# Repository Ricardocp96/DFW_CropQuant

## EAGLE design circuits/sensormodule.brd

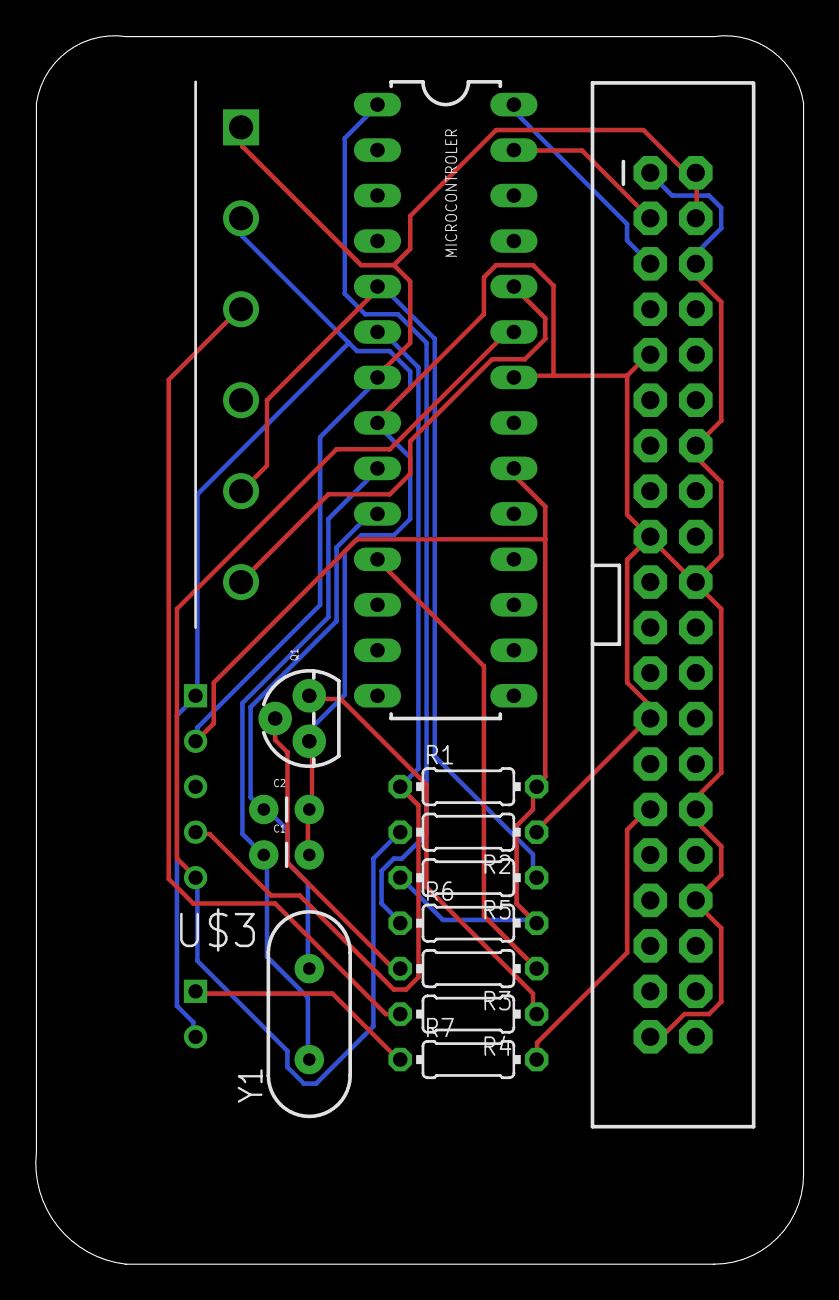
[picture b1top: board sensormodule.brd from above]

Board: 2 copper layers, 42.9 x 68.6 mm, 16 parts (0 on the bottom side), 17 nets.

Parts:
C1, C2: 22pF; CAP-PTH-SMALL
ENVIRONMENTAL_SENSOR: ENV_OUT
MICROCONTROLER: ATMEGA328P_PDIP; DIL28-3
Q1: TO-92
R1, R2: 10K; 0204/7
R3: 1K; 0204/7
R4: 100; 0204/7
R5, R6: 4.7K; 0204/7
R7: 68; 0204/7
SINGLE_BOARD_COMPUTER: RASPBERRYPI-40-PIN-GPIO; 2X20-SHROUDED
SOIL_SENSOR: SOIL_OUT
U$3: LED
Y1: 16MHz; HC49US

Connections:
3.3V: C1.2, C2.2, ENVIRONMENTAL_SENSOR.1, MICROCONTROLER.8, MICROCONTROLER.22, Q1.1, R2.1, SINGLE_BOARD_COMPUTER.1, SINGLE_BOARD_COMPUTER.6, SINGLE_BOARD_COMPUTER.9, SINGLE_BOARD_COMPUTER.14, SINGLE_BOARD_COMPUTER.17, SINGLE_BOARD_COMPUTER.20, SINGLE_BOARD_COMPUTER.25, SINGLE_BOARD_COMPUTER.30, SINGLE_BOARD_COMPUTER.34, SINGLE_BOARD_COMPUTER.39, SOIL_SENSOR.2, U$3.2
5V: ENVIRONMENTAL_SENSOR.2, MICROCONTROLER.7, MICROCONTROLER.20, R1.2, R5.2, R6.2, SINGLE_BOARD_COMPUTER.2, SINGLE_BOARD_COMPUTER.4, SOIL_SENSOR.1
unnamed: C1.1, MICROCONTROLER.9, Y1.1
unnamed: C2.1, MICROCONTROLER.10, Y1.2
unnamed: Q1.3, R4.1
unnamed: ENVIRONMENTAL_SENSOR.5, MICROCONTROLER.23, R2.2
unnamed: MICROCONTROLER.27, SINGLE_BOARD_COMPUTER.3
unnamed: MICROCONTROLER.5, R5.1, SOIL_SENSOR.5
unnamed: ENVIRONMENTAL_SENSOR.4, MICROCONTROLER.6, R1.1
unnamed: MICROCONTROLER.11, R3.1
unnamed: Q1.2, R3.2
unnamed: R4.2, SOIL_SENSOR.3
unnamed: MICROCONTROLER.24, SOIL_SENSOR.6
unnamed: MICROCONTROLER.28, SINGLE_BOARD_COMPUTER.5
unnamed: MICROCONTROLER.1, R6.1
unnamed: R7.1, U$3.1
unnamed: R7.2, SINGLE_BOARD_COMPUTER.29

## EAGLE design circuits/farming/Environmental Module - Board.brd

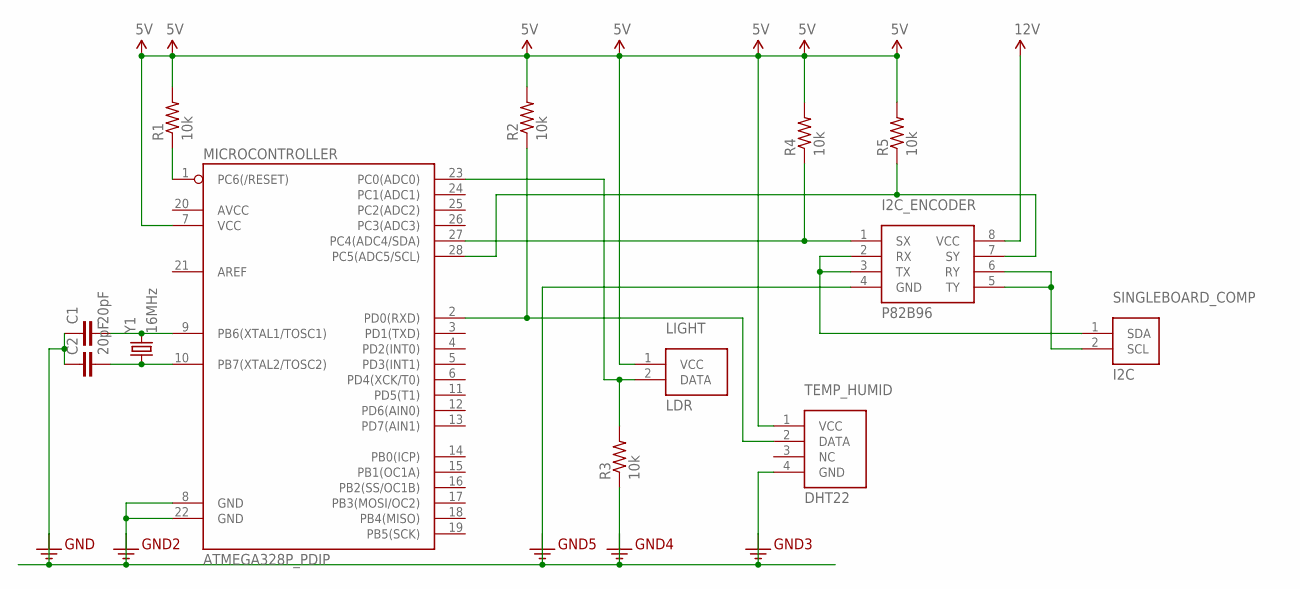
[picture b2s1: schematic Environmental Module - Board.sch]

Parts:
C1, C2: 20pF; CAP-PTH-SMALL
I2C_ENCODER: P82B96; SOIC8
LIGHT: LDR
MICROCONTROLLER: ATMEGA328P_PDIP; DIL28-3
R1, R2, R3, R4, R5: 10k; 0204/7
SINGLEBOARD_COMP: I2C; LDR
TEMP_HUMID: DHT22
Y1: 16MHz; HC49US

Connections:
3.3V: C1.1, C2.1, I2C_ENCODER.4 (GND), MICROCONTROLLER.8 (GND), MICROCONTROLLER.22 (GND), R3.1, TEMP_HUMID.4 (GND)
5V: LIGHT.1 (VCC), MICROCONTROLLER.7 (VCC), R1.2, R2.2, R4.2, R5.2, TEMP_HUMID.1 (VCC)
12V: I2C_ENCODER.8 (VCC)
unnamed: I2C_ENCODER.7 (SY), MICROCONTROLLER.28 (PC5(ADC5/SCL)), R5.1
unnamed: MICROCONTROLLER.1 (PC6(/RESET)), R1.1
unnamed: I2C_ENCODER.5 (TY), I2C_ENCODER.6 (RY), SINGLEBOARD_COMP.2 (SCL)
unnamed: I2C_ENCODER.1 (SX), MICROCONTROLLER.27 (PC4(ADC4/SDA)), R4.1
unnamed: MICROCONTROLLER.2 (PD0(RXD)), R2.1, TEMP_HUMID.2 (DATA)
unnamed: LIGHT.2 (DATA), MICROCONTROLLER.23 (PC0(ADC0)), R3.2
unnamed: I2C_ENCODER.2 (RX), I2C_ENCODER.3 (TX), SINGLEBOARD_COMP.1 (SDA)
unnamed: C2.2, MICROCONTROLLER.10 (PB7(XTAL2/TOSC2)), Y1.1
unnamed: C1.2, MICROCONTROLLER.9 (PB6(XTAL1/TOSC1)), Y1.2

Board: 2 copper layers, 13 parts (0 on the bottom side), 11 nets, no tracks yet.

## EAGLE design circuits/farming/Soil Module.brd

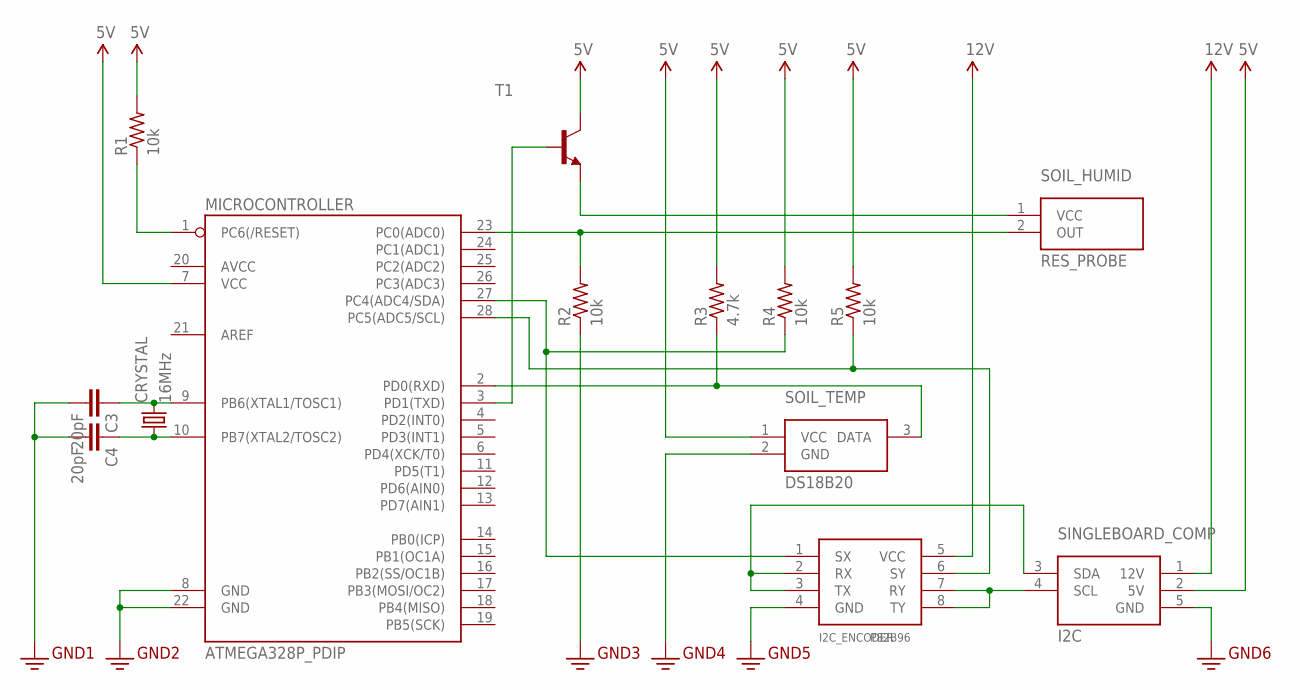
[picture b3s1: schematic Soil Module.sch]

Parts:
C3, C4: 20pF; CAP-PTH-SMALL
CRYSTAL: 16MHz; HC49US
I2C_ENCODER: P82B96; DIP08
MICROCONTROLLER: ATMEGA328P_PDIP; DIL28-3
R1, R2, R4, R5: 10k; 0204/7
R3: 4.7k; 0204/7
SINGLEBOARD_COMP: I2C; I2C_TERM
SOIL_HUMID: RES_PROBE; SOIL_MOISTURE
SOIL_TEMP: DS18B20; SOIL_TEMP
T1: 2N2222A-NPN-TO18-EBC; TO18

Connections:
3.3V: C3.2, C4.2, I2C_ENCODER.4 (GND), MICROCONTROLLER.8 (GND), MICROCONTROLLER.22 (GND), R2.1, SINGLEBOARD_COMP.5 (GND), SOIL_TEMP.2 (GND)
5V: MICROCONTROLLER.7 (VCC), R1.2, R3.2, R4.2, R5.2, SINGLEBOARD_COMP.2 (5V), SOIL_TEMP.1 (VCC), T1.3 (C)
12V: I2C_ENCODER.5 (VCC), SINGLEBOARD_COMP.1 (12V)
unnamed: I2C_ENCODER.6 (SY), MICROCONTROLLER.28 (PC5(ADC5/SCL)), R5.1
unnamed: I2C_ENCODER.1 (SX), MICROCONTROLLER.27 (PC4(ADC4/SDA)), R4.1
unnamed: I2C_ENCODER.2 (RX), I2C_ENCODER.3 (TX), SINGLEBOARD_COMP.3 (SDA)
unnamed: SOIL_HUMID.1 (VCC), T1.1 (E)
unnamed: MICROCONTROLLER.3 (PD1(TXD)), T1.2 (B)
unnamed: MICROCONTROLLER.2 (PD0(RXD)), R3.1, SOIL_TEMP.3 (DATA)
unnamed: MICROCONTROLLER.23 (PC0(ADC0)), R2.2, SOIL_HUMID.2 (OUT)
unnamed: C4.1, CRYSTAL.1, MICROCONTROLLER.10 (PB7(XTAL2/TOSC2))
unnamed: C3.1, CRYSTAL.2, MICROCONTROLLER.9 (PB6(XTAL1/TOSC1))
unnamed: MICROCONTROLLER.1 (PC6(/RESET)), R1.1
unnamed: I2C_ENCODER.7 (RY), I2C_ENCODER.8 (TY), SINGLEBOARD_COMP.4 (SCL)

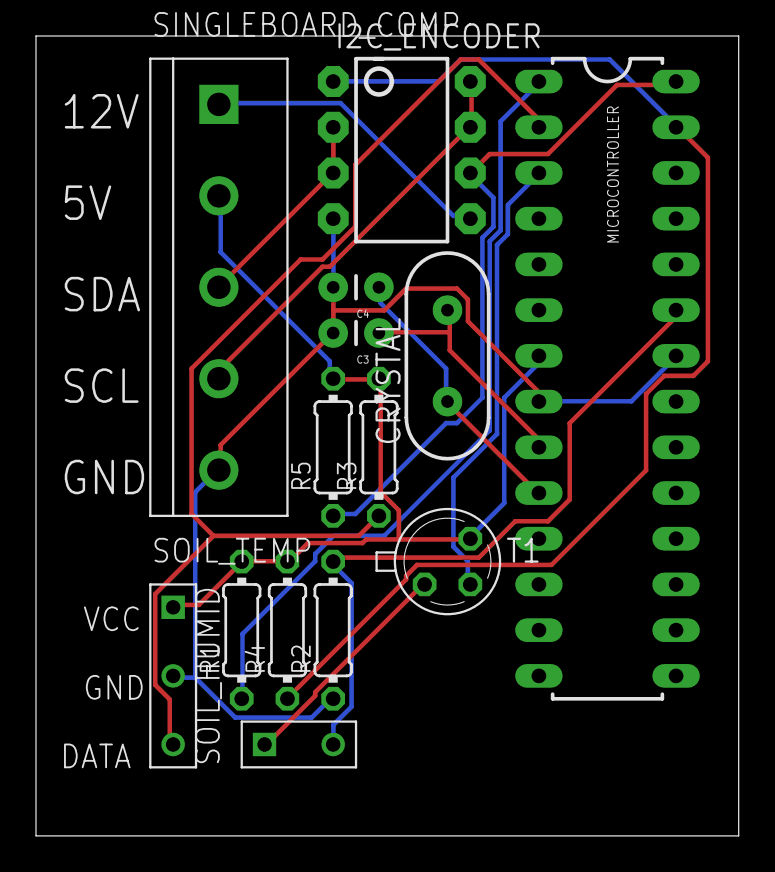
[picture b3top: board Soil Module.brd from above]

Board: 2 copper layers, 39.0 x 44.4 mm, 14 parts (0 on the bottom side), 14 nets.

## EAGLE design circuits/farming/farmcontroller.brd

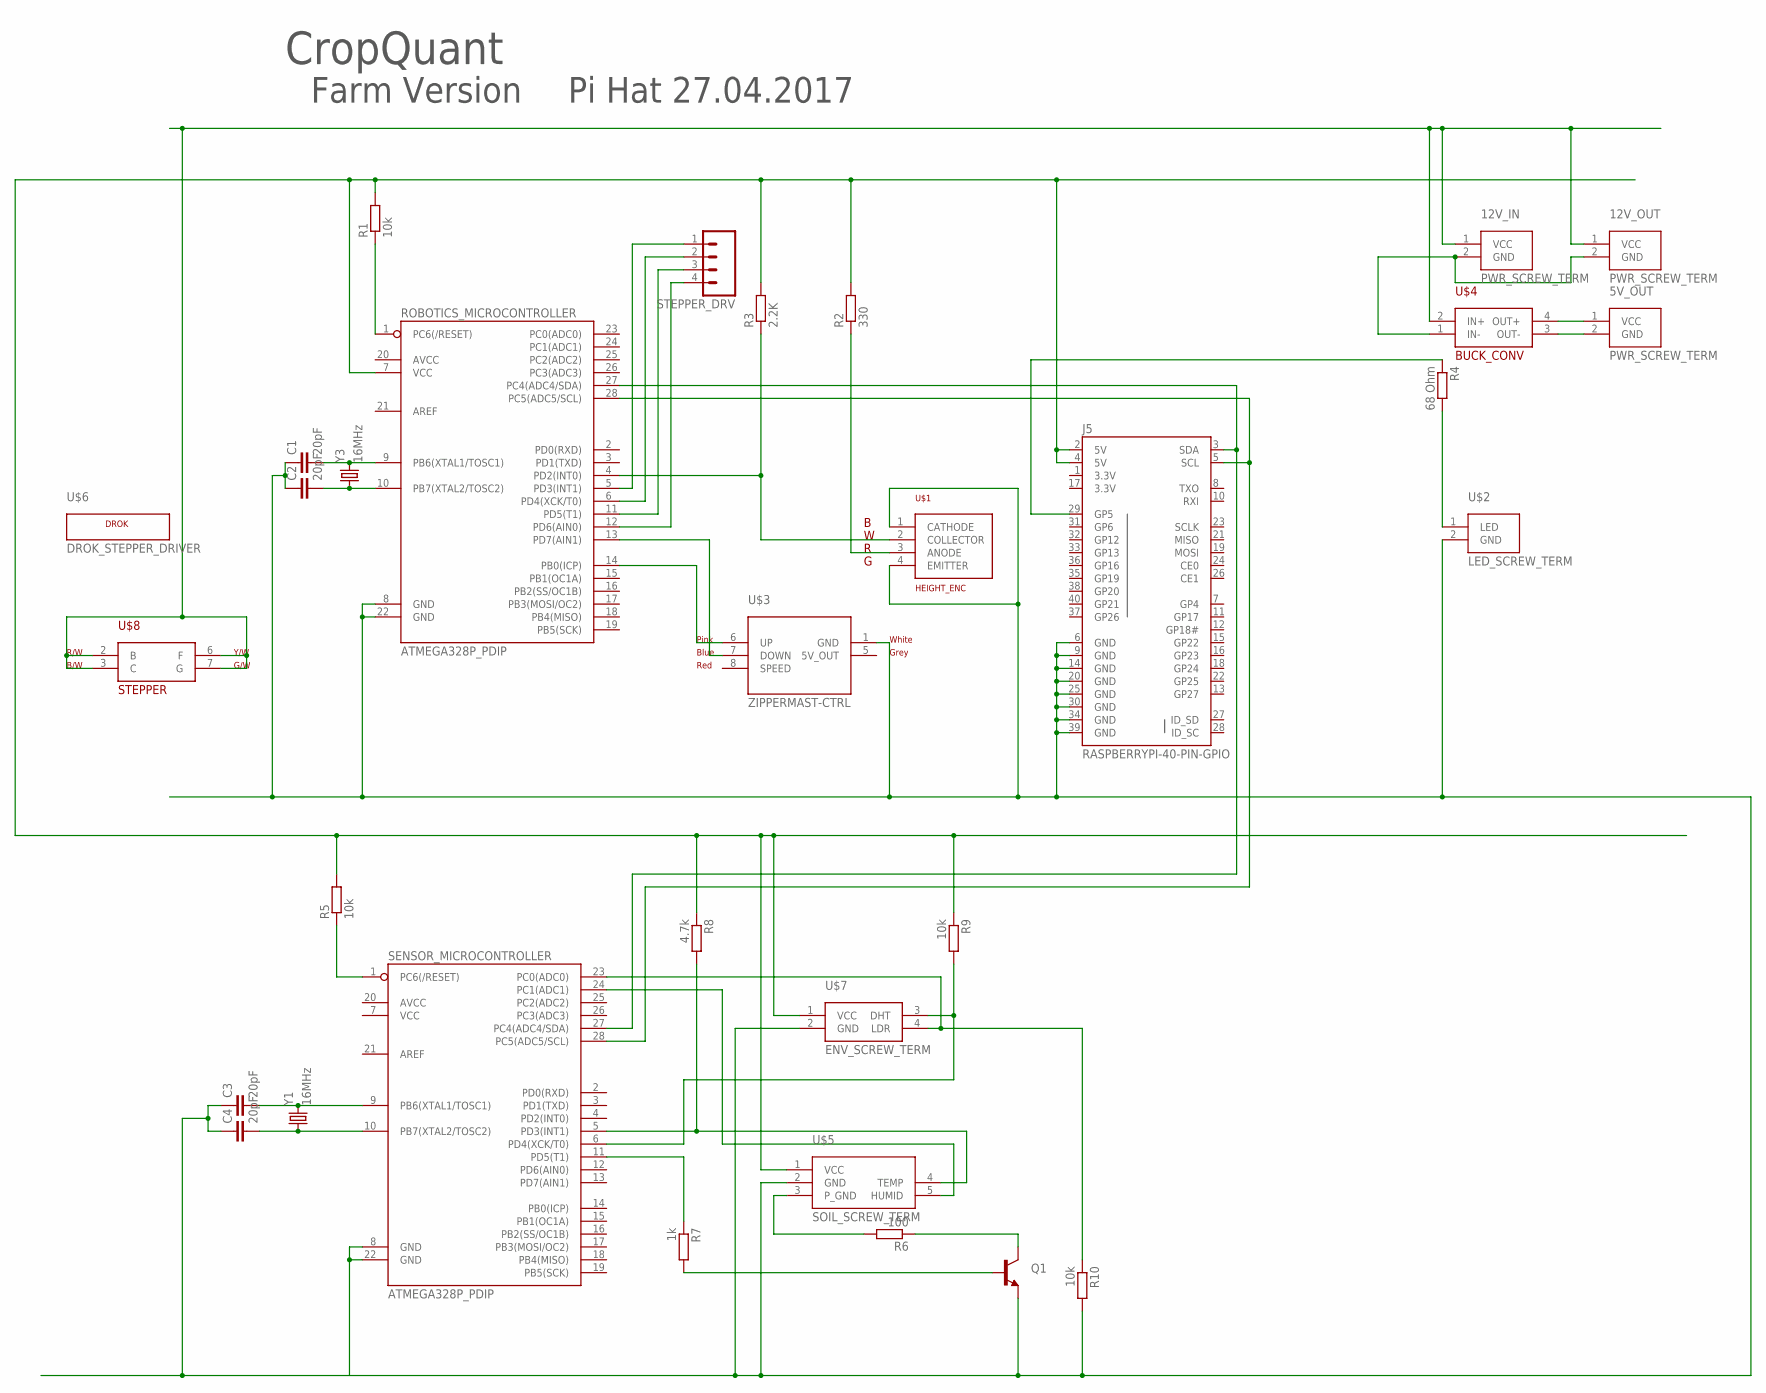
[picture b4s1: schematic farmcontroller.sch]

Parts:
5V_OUT, 12V_IN, 12V_OUT: PWR_SCREW_TERM
C1, C2, C3, C4: 20pF; CAP-PTH-SMALL
J5: RASPBERRYPI-40-PIN-GPIO; 2X20-SHROUDED
Q1: TRANSISTOR_NPNP2N2222A; TO-92
R1, R5, R9, R10: 10k; 0204/7
R2: 330; 0204/7
R3: 2.2K; 0204/7
R4: 68 Ohm; 0204/7
R6: 100; 0204/7
R7: 1k; 0204/7
R8: 4.7k; 0204/7
ROBOTICS_MICROCONTROLLER: ATMEGA328P_PDIP; DIL28-3
SENSOR_MICROCONTROLLER: ATMEGA328P_PDIP; DIL28-3
STEPPER_DRV: M04PTH; 1X04
U$1: HEIGHT_ENC
U$2: LED_SCREW_TERM
U$3: ZIPPERMAST-CTRL
U$4: BUCK_CONV
U$5: SOIL_SCREW_TERM
U$6: DROK_STEPPER_DRIVER
U$7: ENV_SCREW_TERM
U$8: STEPPER
Y1, Y3: 16MHz; HC49US

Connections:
3.3V: J5.1 (3.3V), J5.17 (3.3V)
unnamed: R6.2, U$5.3 (P_GND)
unnamed: J5.2 (5V), J5.4 (5V), R1.2, R2.2, R3.2, R5.2, R8.1, R9.1, ROBOTICS_MICROCONTROLLER.7 (VCC), U$5.1 (VCC), U$7.1 (VCC)
unnamed: R1.1, ROBOTICS_MICROCONTROLLER.1 (PC6(/RESET))
unnamed: J5.3 (SDA), ROBOTICS_MICROCONTROLLER.27 (PC4(ADC4/SDA)), SENSOR_MICROCONTROLLER.27 (PC4(ADC4/SDA))
unnamed: J5.5 (SCL), ROBOTICS_MICROCONTROLLER.28 (PC5(ADC5/SCL)), SENSOR_MICROCONTROLLER.28 (PC5(ADC5/SCL))
unnamed: ROBOTICS_MICROCONTROLLER.14 (PB0(ICP)), U$3.6 (UP)
unnamed: ROBOTICS_MICROCONTROLLER.13 (PD7(AIN1)), U$3.7 (DOWN)
unnamed: R5.1, SENSOR_MICROCONTROLLER.1 (PC6(/RESET))
unnamed: R2.1, U$1.3 (ANODE)
unnamed: R3.1, ROBOTICS_MICROCONTROLLER.4 (PD2(INT0)), U$1.2 (COLLECTOR)
unnamed: 12V_IN.1 (VCC), 12V_OUT.1 (VCC), U$4.2 (IN+), U$8.2 (B), U$8.3 (C), U$8.6 (F), U$8.7 (G)
unnamed: C2.2, ROBOTICS_MICROCONTROLLER.10 (PB7(XTAL2/TOSC2)), Y3.1
unnamed: C3.2, SENSOR_MICROCONTROLLER.9 (PB6(XTAL1/TOSC1)), Y1.2
unnamed: R4.2, U$2.1 (LED)
unnamed: J5.29 (GP5), R4.1
unnamed: C4.2, SENSOR_MICROCONTROLLER.10 (PB7(XTAL2/TOSC2)), Y1.1
unnamed: 12V_IN.2 (GND), 12V_OUT.2 (GND), U$4.1 (IN-)
unnamed: 5V_OUT.1 (VCC), U$4.4 (OUT+)
unnamed: 5V_OUT.2 (GND), U$4.3 (OUT-)
unnamed: C1.2, ROBOTICS_MICROCONTROLLER.9 (PB6(XTAL1/TOSC1)), Y3.2
unnamed: Q1.1 (C), R6.1
unnamed: C1.1, C2.1, C3.1, C4.1, J5.6 (GND), J5.9 (GND), J5.14 (GND), J5.20 (GND), J5.25 (GND), J5.30 (GND), J5.34 (GND), J5.39 (GND), Q1.3 (E), R10.2, ROBOTICS_MICROCONTROLLER.8 (GND), ROBOTICS_MICROCONTROLLER.22 (GND), SENSOR_MICROCONTROLLER.8 (GND), SENSOR_MICROCONTROLLER.22 (GND), U$1.1 (CATHODE), U$1.4 (EMITTER), U$2.2 (GND), U$3.1 (GND), U$5.2 (GND), U$7.2 (GND)
unnamed: Q1.2 (B), R7.2
unnamed: ROBOTICS_MICROCONTROLLER.5 (PD3(INT1)), STEPPER_DRV.1
unnamed: R7.1, SENSOR_MICROCONTROLLER.11 (PD5(T1))
unnamed: ROBOTICS_MICROCONTROLLER.6 (PD4(XCK/T0)), STEPPER_DRV.2
unnamed: ROBOTICS_MICROCONTROLLER.11 (PD5(T1)), STEPPER_DRV.3
unnamed: ROBOTICS_MICROCONTROLLER.12 (PD6(AIN0)), STEPPER_DRV.4
unnamed: SENSOR_MICROCONTROLLER.24 (PC1(ADC1)), U$5.5 (HUMID)
unnamed: R8.2, SENSOR_MICROCONTROLLER.5 (PD3(INT1)), U$5.4 (TEMP)
unnamed: R9.2, SENSOR_MICROCONTROLLER.6 (PD4(XCK/T0)), U$7.3 (DHT)
unnamed: R10.1, SENSOR_MICROCONTROLLER.23 (PC0(ADC0)), U$7.4 (LDR)

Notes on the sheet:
CropQuant
Farm Version
Pi Hat 27.04.2017

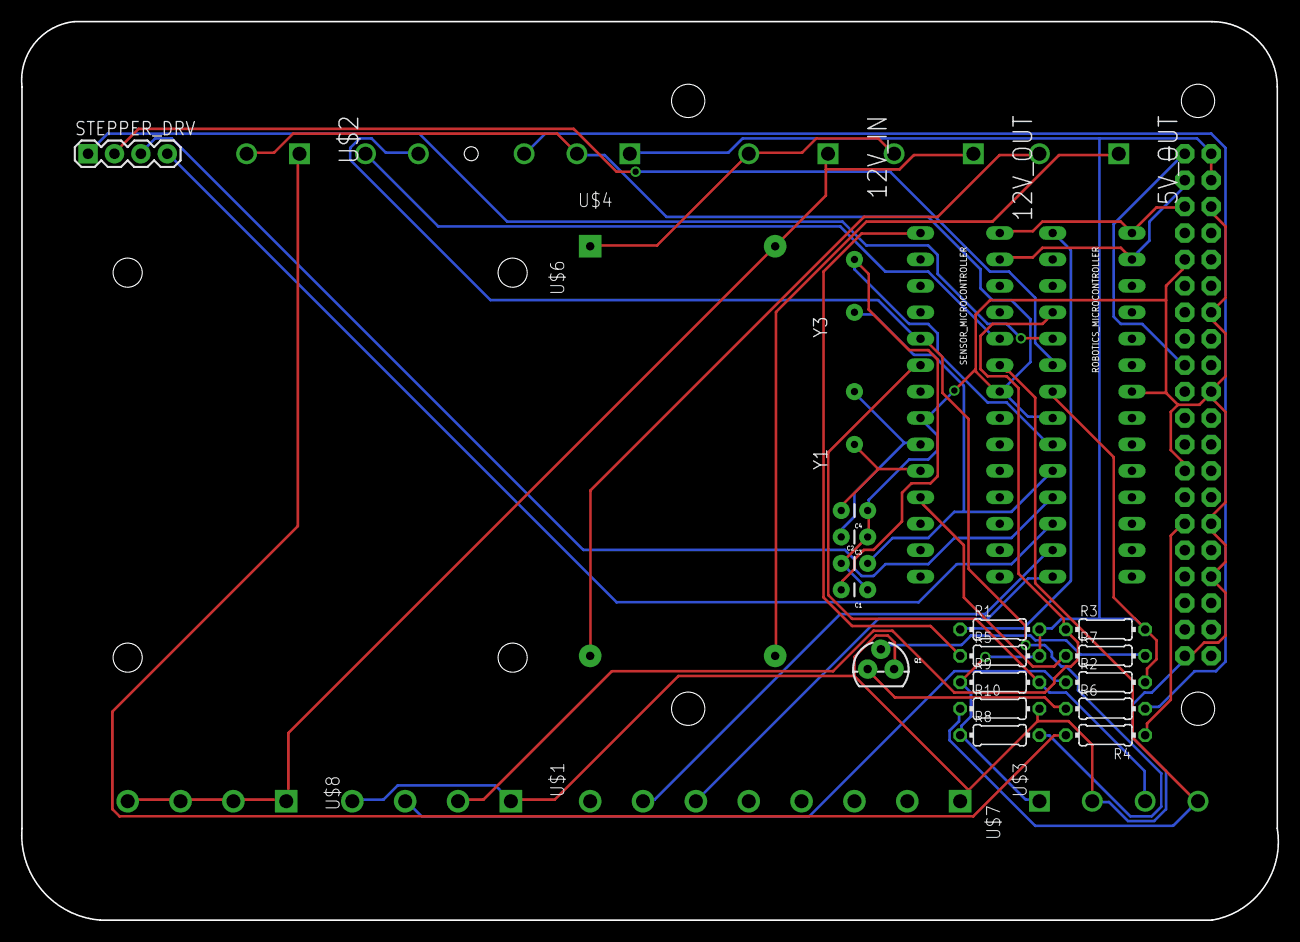
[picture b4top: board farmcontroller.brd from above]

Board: 2 copper layers, 120.8 x 86.4 mm, 32 parts (0 on the bottom side), 33 nets.

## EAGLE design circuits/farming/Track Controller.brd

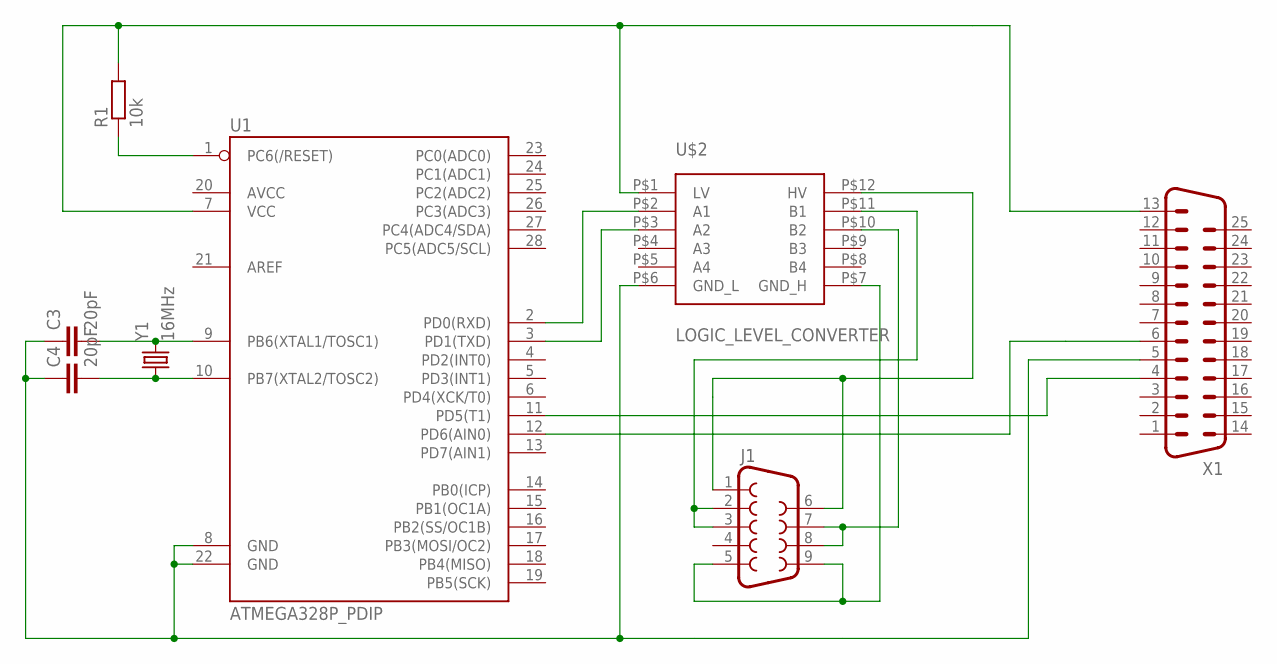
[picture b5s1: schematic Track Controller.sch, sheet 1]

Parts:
C3, C4: 20pF; CAP-PTH-5MM
J1: DB9FEMALE; DB9
R1: 10k; 0204/7
U1: ATMEGA328P_PDIP; DIL28-3
U$2: LOGIC_LEVEL_CONVERTER
X1: DB25H; M25H
Y1: 16MHz; HC49US

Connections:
unnamed: R1.2, U1.7 (VCC), U$2.P$1 (LV), X1.13
unnamed: C3.1, C4.1, U1.8 (GND), U1.22 (GND), U$2.P$6 (GND_L), X1.5
unnamed: U1.12 (PD6(AIN0)), X1.6
unnamed: U1.11 (PD5(T1)), X1.4
unnamed: U1.2 (PD0(RXD)), U$2.P$2 (A1)
unnamed: U1.3 (PD1(TXD)), U$2.P$3 (A2)
unnamed: J1.7, J1.8, U$2.P$10 (B2)
unnamed: J1.1, J1.6, U$2.P$12 (HV)
unnamed: J1.5, J1.9, U$2.P$7 (GND_H)
unnamed: R1.1, U1.1 (PC6(/RESET))
unnamed: J1.2, J1.3, U$2.P$11 (B1)
unnamed: C3.2, U1.9 (PB6(XTAL1/TOSC1)), Y1.2
unnamed: C4.2, U1.10 (PB7(XTAL2/TOSC2)), Y1.1

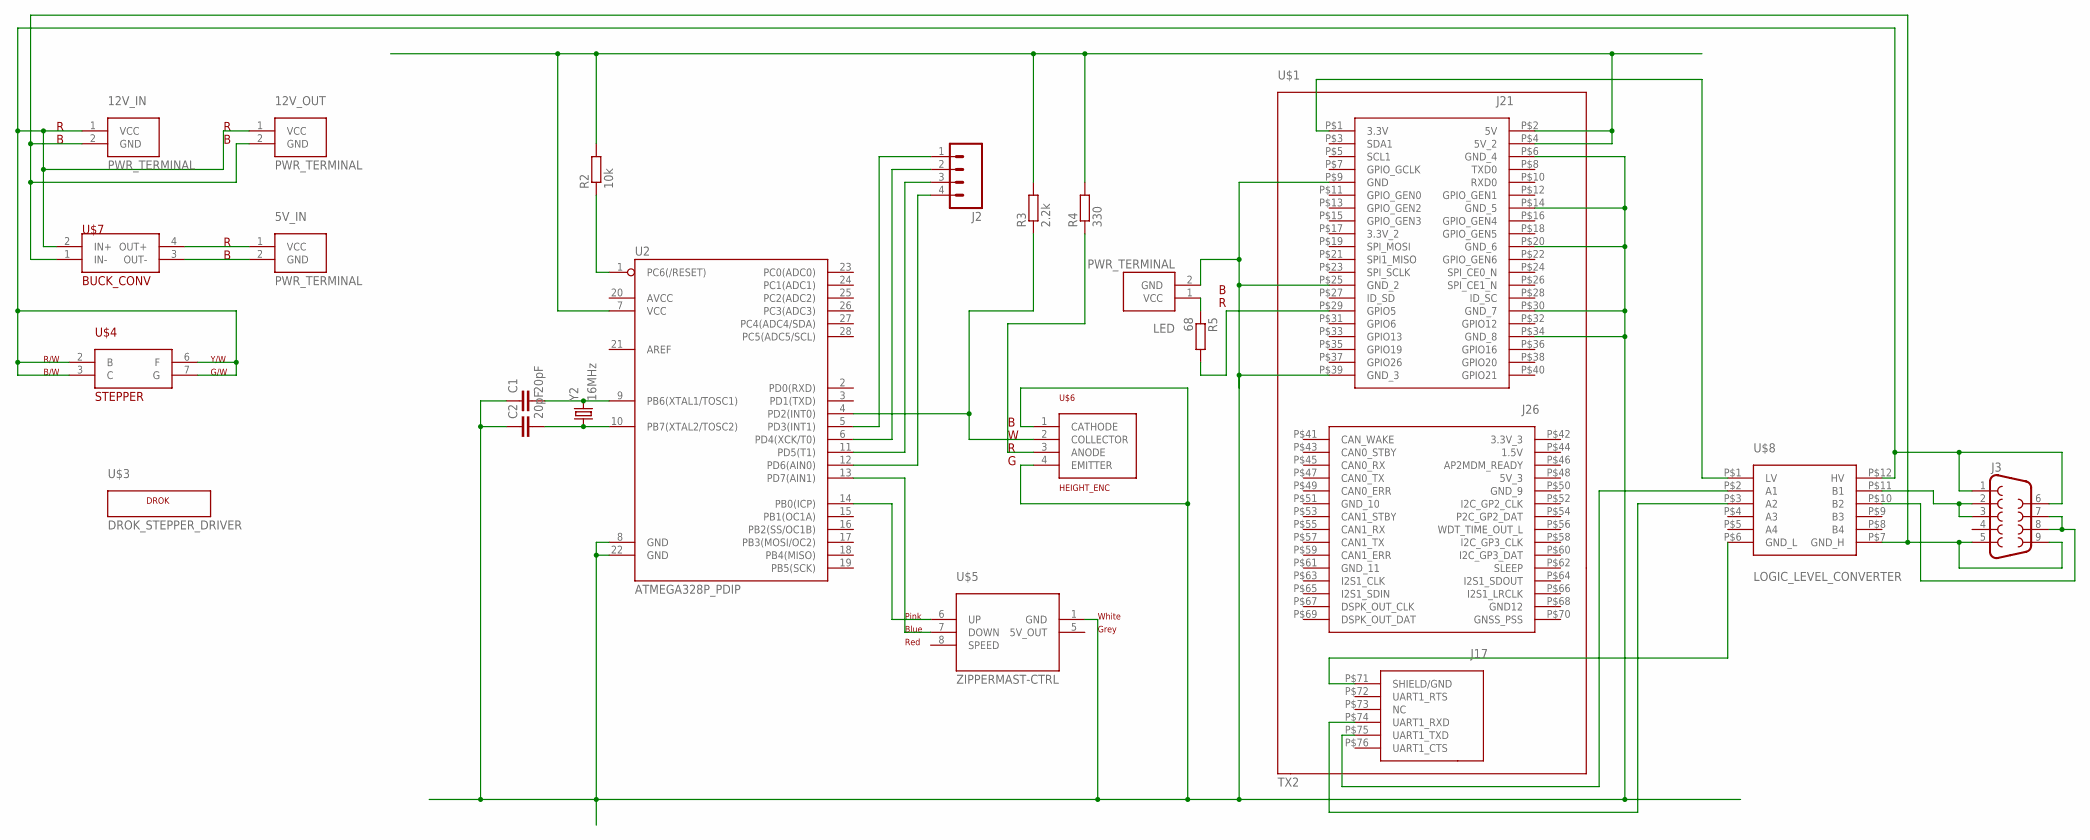
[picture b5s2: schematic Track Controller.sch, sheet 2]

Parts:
5V_IN, 12V_IN, 12V_OUT: PWR_TERMINAL
C1, C2: 20pF; CAP-PTH-5MM
J2: M04PTH; 1X04
J3: DB9MALE; DB9_MALE
LED: PWR_TERMINAL
R2: 10k; 0204/7
R3: 2.2k; 0204/7
R4: 330; 0204/7
R5: 68; 0204/7
U2: ATMEGA328P_PDIP; DIL28-3
U$1: TX2
U$3: DROK_STEPPER_DRIVER
U$4: STEPPER
U$5: ZIPPERMAST-CTRL
U$6: HEIGHT_ENC
U$7: BUCK_CONV
U$8: LOGIC_LEVEL_CONVERTER
Y2: 16MHz; HC49US

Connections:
unnamed: J2.1, U2.5 (PD3(INT1))
unnamed: R2.2, R3.2, R4.2, U2.7 (VCC), U$1.P$2 (5V), U$1.P$4 (5V_2)
unnamed: R2.1, U2.1 (PC6(/RESET))
unnamed: J2.2, U2.6 (PD4(XCK/T0))
unnamed: LED.1 (VCC), R5.1
unnamed: J2.3, U2.11 (PD5(T1))
unnamed: J2.4, U2.12 (PD6(AIN0))
unnamed: R3.1, U2.4 (PD2(INT0)), U$6.2 (COLLECTOR)
unnamed: R4.1, U$6.3 (ANODE)
unnamed: U$1.P$75 (UART1_TXD), U$8.P$2 (A1)
unnamed: 5V_IN.2 (GND), U$7.3 (OUT-)
unnamed: 5V_IN.1 (VCC), U$7.4 (OUT+)
unnamed: U2.13 (PD7(AIN1)), U$5.7 (DOWN)
unnamed: U2.14 (PB0(ICP)), U$5.6 (UP)
unnamed: C1.2, U2.9 (PB6(XTAL1/TOSC1)), Y2.2
unnamed: U$1.P$74 (UART1_RXD), U$8.P$3 (A2)
unnamed: C2.2, U2.10 (PB7(XTAL2/TOSC2)), Y2.1
unnamed: C1.1, C2.1, LED.2 (GND), U2.8 (GND), U2.22 (GND), U$1.P$6 (GND_4), U$1.P$9 (GND), U$1.P$14 (GND_5), U$1.P$20 (GND_6), U$1.P$25 (GND_2), U$1.P$30 (GND_7), U$1.P$34 (GND_8), U$1.P$39 (GND_3), U$5.1 (GND), U$6.1 (CATHODE), U$6.4 (EMITTER)
unnamed: R5.2, U$1.P$29 (GPIO5)
unnamed: U$1.P$1 (3.3V), U$8.P$1 (LV)
unnamed: U$1.P$71 (SHIELD/GND), U$8.P$6 (GND_L)
unnamed: 12V_IN.1 (VCC), 12V_OUT.1 (VCC), J3.1, J3.6, U$4.2 (B), U$4.3 (C), U$4.6 (F), U$4.7 (G), U$7.2 (IN+), U$8.P$12 (HV)
unnamed: 12V_IN.2 (GND), 12V_OUT.2 (GND), J3.5, J3.9, U$7.1 (IN-), U$8.P$7 (GND_H)
unnamed: J3.7, J3.8, U$8.P$10 (B2)
unnamed: J3.2, J3.3, U$8.P$11 (B1)

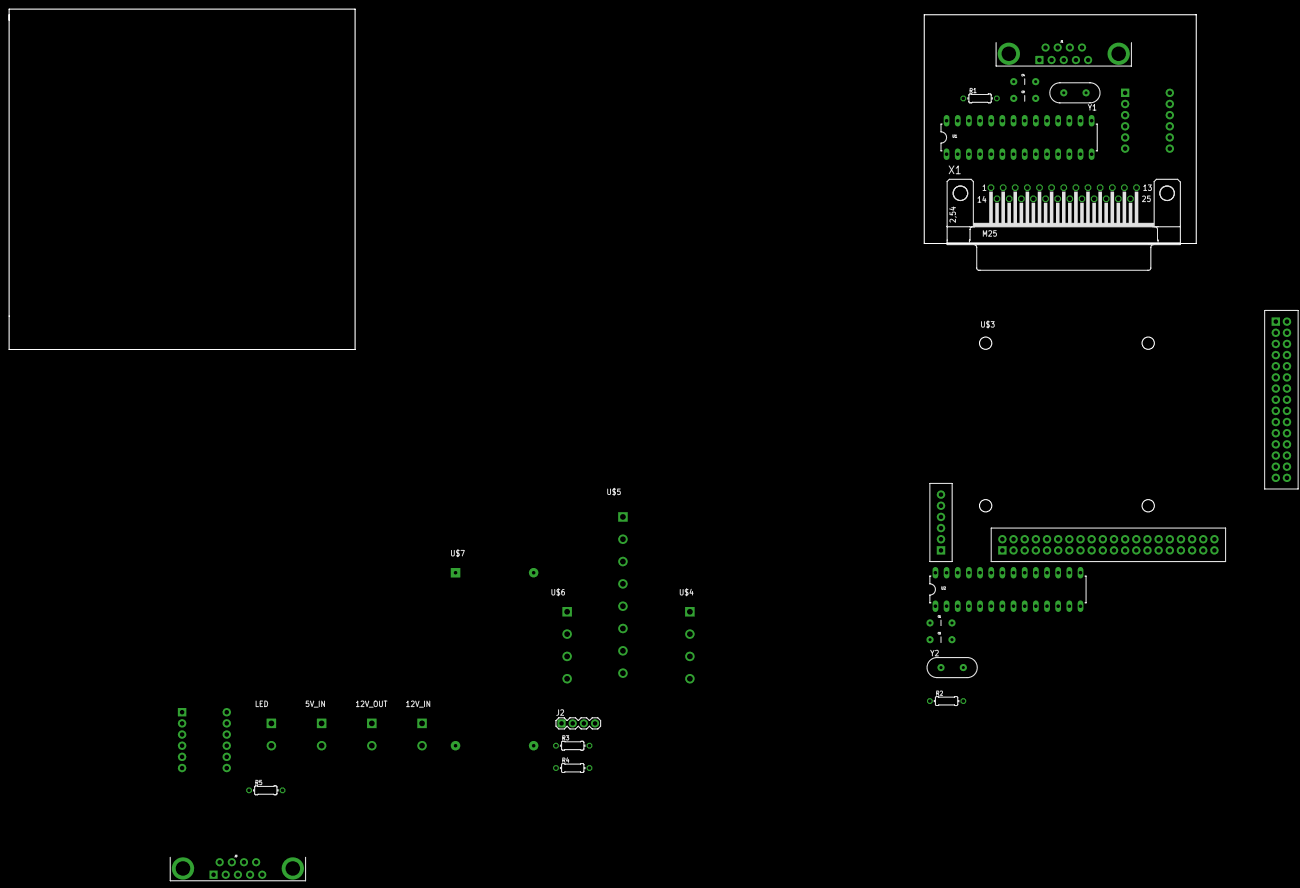
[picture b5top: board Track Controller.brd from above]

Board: 2 copper layers, 29 parts (0 on the bottom side), 38 nets.

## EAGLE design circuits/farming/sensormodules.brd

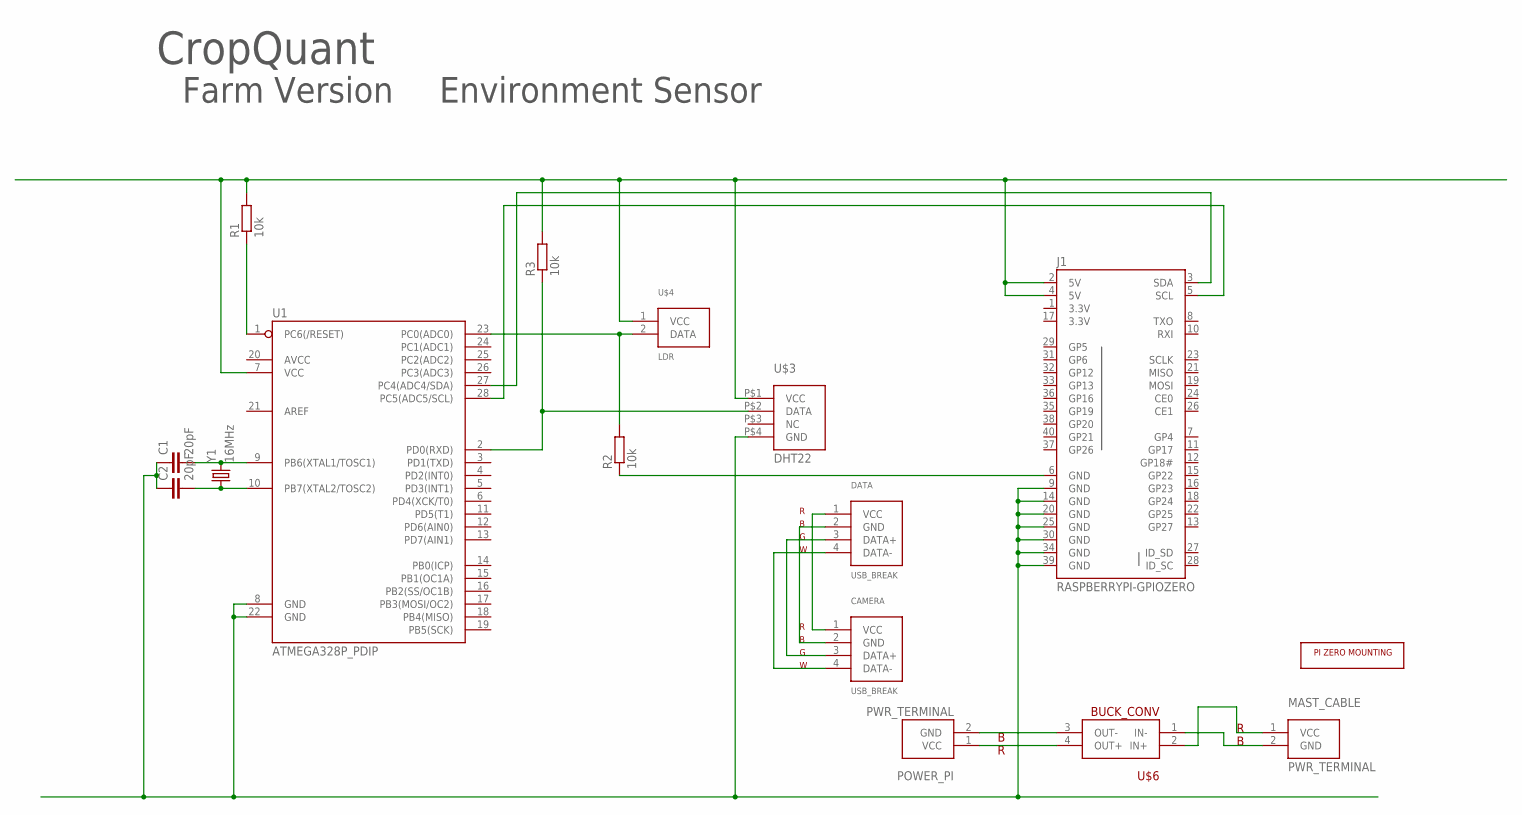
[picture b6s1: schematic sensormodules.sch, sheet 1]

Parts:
C1, C2: 20pF; CAP-PTH-SMALL
CAMERA: USB_BREAK
DATA: USB_BREAK
J1: RASPBERRYPI-GPIOZERO; 2X20-ZERO
MAST_CABLE: PWR_TERMINAL
POWER_PI: PWR_TERMINAL
R1, R2, R3: 10k; 0204/7
U1: ATMEGA328P_PDIP; DIL28-3
U$3: DHT22
U$4: LDR
U$5: PI_ZERO_MOUNT; ZERO_MOUNT
U$6: BUCK_CONV
Y1: 16MHz; HC49US

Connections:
3.3V: J1.1 (3.3V), J1.17 (3.3V)
unnamed: J1.2 (5V), J1.4 (5V), R1.2, R3.2, U1.7 (VCC), U$3.P$1 (VCC), U$4.1 (VCC)
unnamed: R1.1, U1.1 (PC6(/RESET))
unnamed: J1.3 (SDA), U1.27 (PC4(ADC4/SDA))
unnamed: J1.5 (SCL), U1.28 (PC5(ADC5/SCL))
unnamed: R3.1, U1.2 (PD0(RXD)), U$3.P$2 (DATA)
unnamed: R2.2, U1.23 (PC0(ADC0)), U$4.2 (DATA)
unnamed: CAMERA.1 (VCC), DATA.1 (VCC)
unnamed: C2.2, U1.10 (PB7(XTAL2/TOSC2)), Y1.1
unnamed: CAMERA.2 (GND), DATA.2 (GND)
unnamed: CAMERA.3 (DATA+), DATA.3 (DATA+)
unnamed: CAMERA.4 (DATA-), DATA.4 (DATA-)
unnamed: POWER_PI.2 (GND), U$6.3 (OUT-)
unnamed: MAST_CABLE.2 (GND), U$6.1 (IN-)
unnamed: C1.2, U1.9 (PB6(XTAL1/TOSC1)), Y1.2
unnamed: J1.6 (GND), R2.1
unnamed: MAST_CABLE.1 (VCC), U$6.2 (IN+)
unnamed: POWER_PI.1 (VCC), U$6.4 (OUT+)
unnamed: C1.1, C2.1, J1.9 (GND), J1.14 (GND), J1.20 (GND), J1.25 (GND), J1.30 (GND), J1.34 (GND), J1.39 (GND), U1.8 (GND), U1.22 (GND), U$3.P$4 (GND)

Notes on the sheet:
CropQuant
Farm Version
Environment Sensor

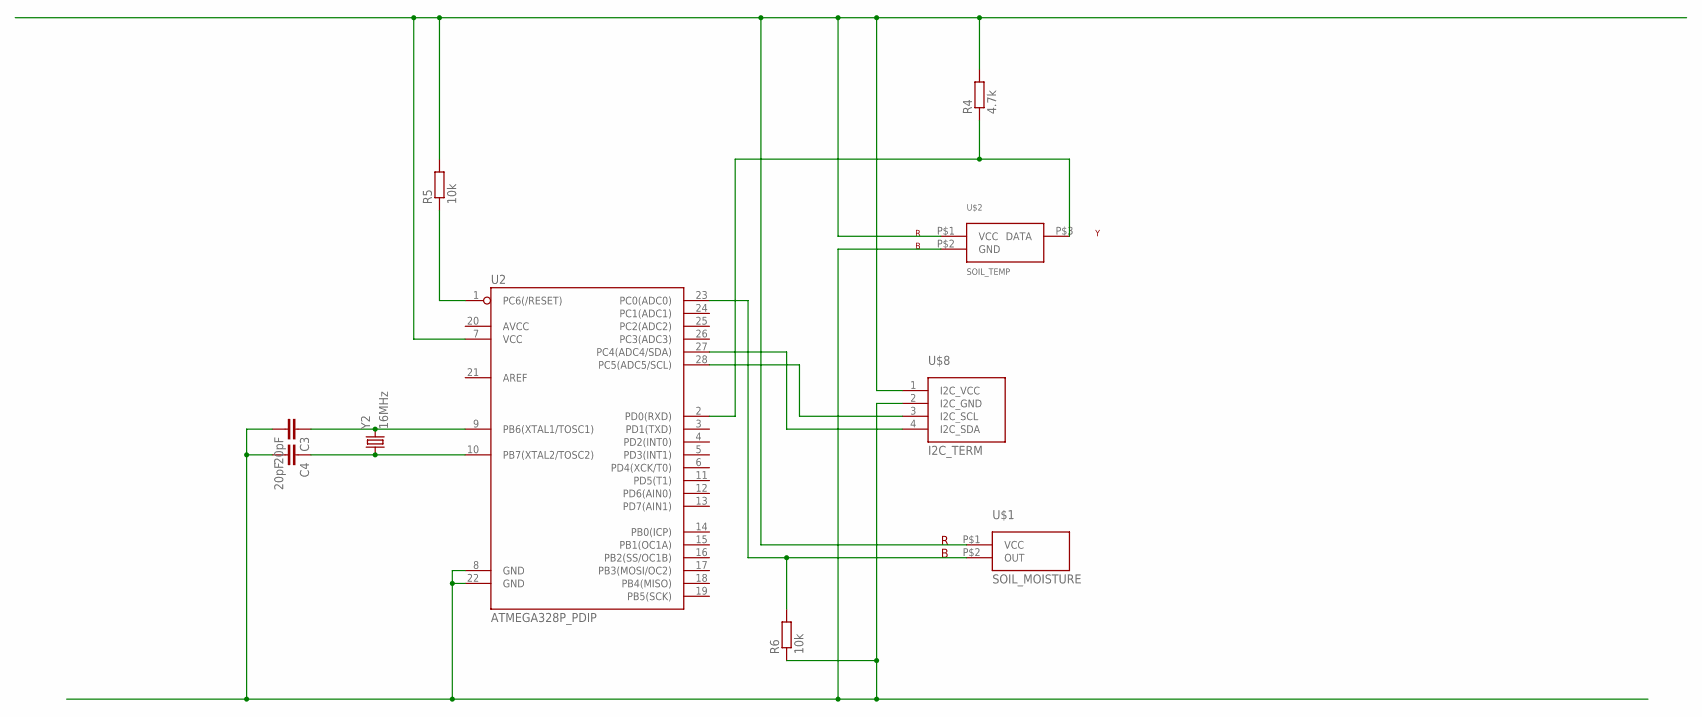
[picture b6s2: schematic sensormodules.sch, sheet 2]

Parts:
C3, C4: 20pF; CAP-PTH-SMALL
R4: 4.7k; 0204/7
R5, R6: 10k; 0204/7
U2: ATMEGA328P_PDIP; DIL28-3
U$1: SOIL_MOISTURE
U$2: SOIL_TEMP
U$8: I2C_TERM
Y2: 16MHz; HC49US

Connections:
unnamed: R4.2, R5.2, U2.7 (VCC), U$1.P$1 (VCC), U$2.P$1 (VCC), U$8.1 (I2C_VCC)
unnamed: R4.1, U2.2 (PD0(RXD)), U$2.P$3 (DATA)
unnamed: R6.2, U2.23 (PC0(ADC0)), U$1.P$2 (OUT)
unnamed: C3.2, C4.2, R6.1, U2.8 (GND), U2.22 (GND), U$2.P$2 (GND), U$8.2 (I2C_GND)
unnamed: C4.1, U2.10 (PB7(XTAL2/TOSC2)), Y2.1
unnamed: C3.1, U2.9 (PB6(XTAL1/TOSC1)), Y2.2
unnamed: R5.1, U2.1 (PC6(/RESET))
unnamed: U2.28 (PC5(ADC5/SCL)), U$8.3 (I2C_SCL)
unnamed: U2.27 (PC4(ADC4/SDA)), U$8.4 (I2C_SDA)

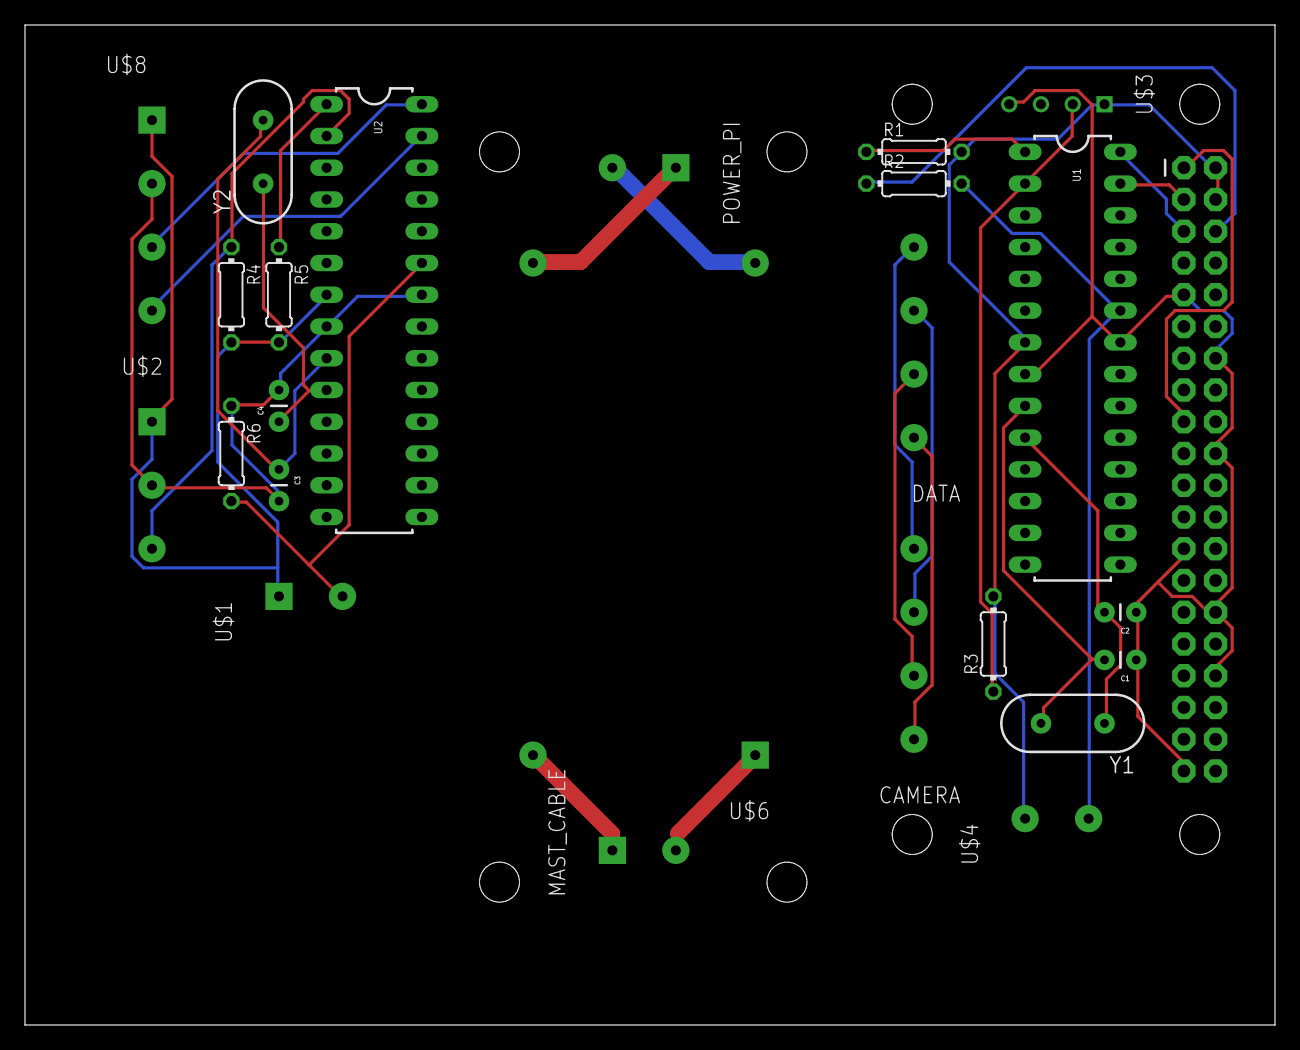
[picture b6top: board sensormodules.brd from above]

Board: 2 copper layers, 100.0 x 80.0 mm, 26 parts (0 on the bottom side), 28 nets.

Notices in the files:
parts and their libraries:
SparkFun-DigitalIC: Licensing: Creative Commons ShareAlike 4.0 International - https://creativecommons.org/licenses/by-sa/4.0
